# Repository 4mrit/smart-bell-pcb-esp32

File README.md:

# Smart Bell PCB Design - ESP32

## Overview

This repository contains the KiCad project files for the PCB design of the Smart Bell system using the ESP32 microcontroller. It includes schematic diagrams, PCB layout files, custom libraries, and project settings.

## Project Structure

- **`/`**: Root directory containing this `README.md` and other documentation.
- **`/`**: Contains KiCad project files for the ESP32 PCB design.
  - **`*.kicad_sch`**: Schematic files for the PCB design.
  - **`*.kicad_pcb`**: PCB layout files.
  - **`*.kicad_pro`**: Project settings and metadata.
  - **`/KICAD_LIBRARIES/`**: Custom libraries and components used in the design.
  - **`/custom/`**: Additional custom components.
  - **`README.md`**: Documentation specific to the ESP32 PCB design.

## Files

- **`*.kicad_sch`**: Schematic diagrams for the PCB.
- **`*.kicad_pcb`**: PCB layout files.
- **`*.kicad_pro`**: Project configuration and settings.
- **`/KICAD_LIBRARIES/`**: Custom KiCad libraries and components.
- **`/custom/`**: Additional custom components and libraries.

## Getting Started

1. **Clone the Repository**: Clone this repository to your local machine.
    ```bash
    git clone https://github.com/4mrit/smart-bell-pcb-esp32.git

2. **Open in KiCad**: Open the .kicad_pro file in KiCad to access the project files.

3. **Review and Modify**: Review the schematic and PCB layout. Modify as necessary for your specific requirements.

4. **Generate Outputs**: Use KiCad to generate PCB manufacturing files, such as Gerbers and Bill of Materials (BoM).

## Documentation
- Schematic Diagrams: Found in *.kicad_sch files.
- PCB Layout: Found in *.kicad_pcb files.
- Libraries: Custom libraries are located in KICAD_LIBRARIES/ and custom/.

## License
This project is licensed under the MIT License.

## Contact
For questions or issues, please contact at `amritpaudel03@gmail.com`.

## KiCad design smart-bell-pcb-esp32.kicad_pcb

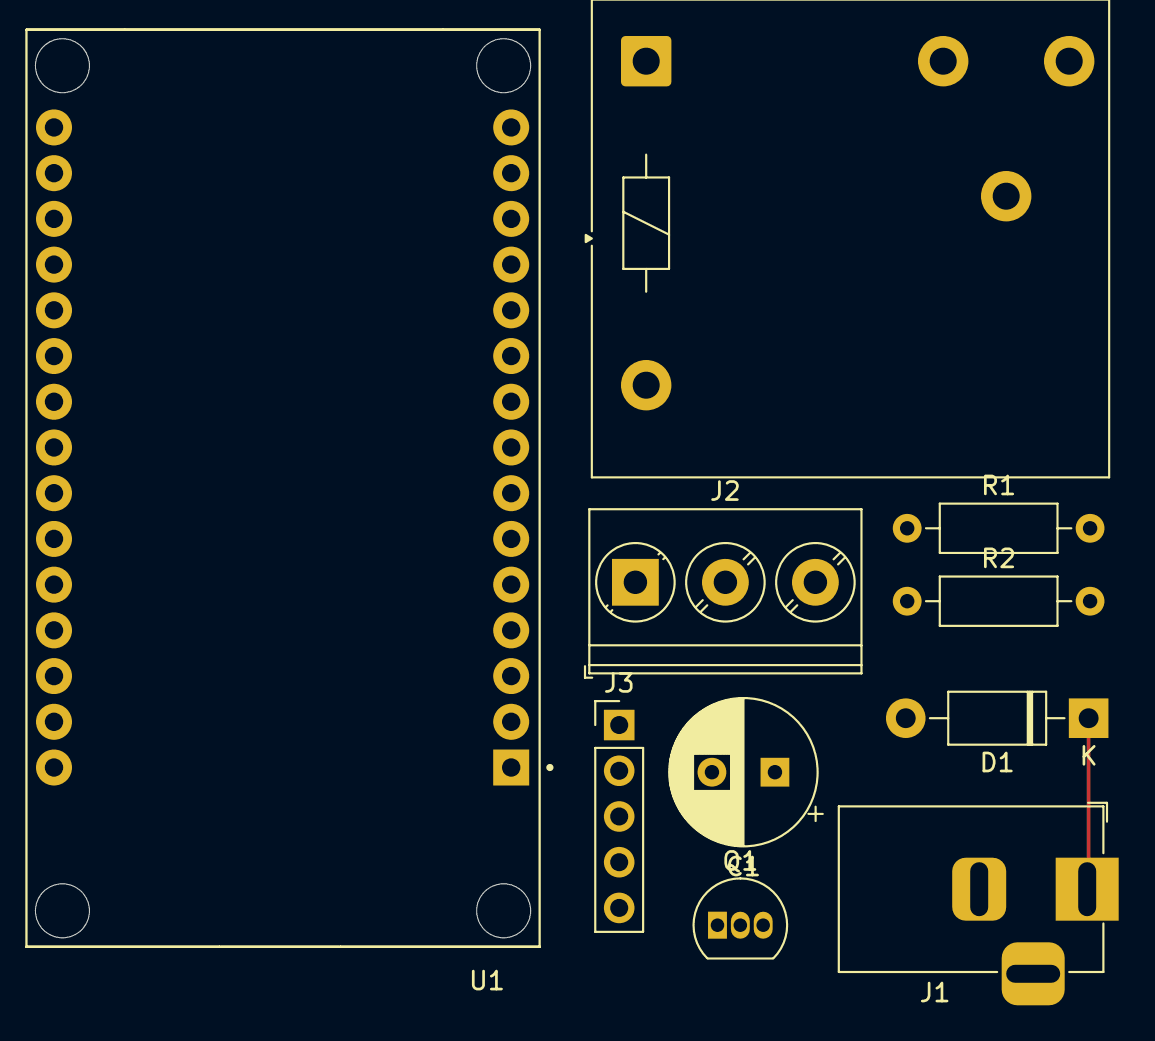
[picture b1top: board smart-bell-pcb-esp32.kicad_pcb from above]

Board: 2 copper layers, 10 parts (0 on the bottom side), 10 nets.

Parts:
C1: C_Polarized_US; CP_Radial_D8.0mm_P3.50mm
D1: 1N4007; D_DO-41_SOD81_P10.16mm_Horizontal
J1: Barrel_Jack_MountingPin; BarrelJack_Horizontal
J2: Screw_Terminal_01x03; TerminalBlock_Phoenix_PT-1,5-3-5.0-H_1x03_P5.00mm_Horizontal
J3: Conn_01x04; PinHeader_1x05_P2.54mm_Vertical
K1: FINDER-40.11; Relay_SPDT_Finder_40.11
Q1: BC547; TO-92_Inline
R1, R2: R; R_Axial_DIN0207_L6.3mm_D2.5mm_P10.16mm_Horizontal
U1: ESP32_DEVKIT_V1

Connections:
+5V: C1.1, D1.1 (K), J1.1, J3.1, K1.A1, U1.30 (VIN)
/RELAY_1_IN: R2.1, U1.15 (D23)
/RTC_CLK: J3.3, U1.14 (D22)
/RTC_DAT: J3.4, U1.11 (D21)
GND: C1.2, J1.2, J3.2, Q1.3 (E), R1.2, U1.2 (GND), U1.29 (GND)
unnamed: D1.2 (A), K1.A2, Q1.1 (C)
unnamed: Q1.2 (B), R1.1, R2.2
RELAY_1_COM: J2.2, K1.11
RELAY_1_NC: J2.3, K1.14
RELAY_1_NO: J2.1, K1.12

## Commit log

2024-07-24 feat: add Project file
2024-07-24 docs: add readme
2024-07-24 docs: update readme
2024-07-25 feat: update sketch
